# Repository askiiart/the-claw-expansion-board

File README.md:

# The Claw Expansion Board

## WARNING: EXTREME HEAT

This design accidentally used an LDO, which can lead to up to ~240 watts of excess heat being generated. Do not use this as it is now! Change the design to use a buck converter instead.

---

Would recommmend swapping it out for a XL4016E1. Will be updated with that eventually.

An expansion board to support further modding for my printer I'm desinging for Blueprint. The goals of this are:

- Power output rails on 24V, 12V, and 5V
- Power + I2C expansion port
- Laser (power/GND/PWM) port
- PNP (vacuum PWR/GND ; solenoid PWR/GND) port
- MOSFET to turn bed on/off, rather than depending on messy external setup
- Able to handle the maximum current (25A, 7.5A for buck converters) anywhere

## Parts

|Item                                |Price |Quantity|Link                                                                                 |Total Cost|Notes                                                          |
|------------------------------------|------|--------|-------------------------------------------------------------------------------------|----------|---------------------------------------------------------------|
|COS29752WU (LDO regulator)          |$2.10 |2       |https://www.lcsc.com/product-detail/C41428569.html                                   |$4.20     |                                                               |
|XD8574AP (I/O expander)             |$0.57 |1       |https://www.lcsc.com/product-detail/C561268.html                                     |$0.57     |                                                               |
|DB125-2.54-4P-GN-S (4P screw term)  |$0.40 |2       |https://www.lcsc.com/product-detail/C918122.html                                     |$0.80     |                                                               |
|DB125-2.54-3P-GN-S (3P screw term)  |$0.33 |1       |https://www.lcsc.com/product-detail/C918121.html                                     |$1.67     |                                                               |
|MS50N06 (50A NMOS)                  |$0.11 |4       |https://www.lcsc.com/product-detail/C2902884.html                                    |$0.57     |                                                               |
|AO3400A (5.8A NMOS)                 |$0.03 |1       |https://www.lcsc.com/product-detail/C347475.html                                     |$0.65     |                                                               |
|BSS84 (PMOS)                        |$0.01 |1       |https://www.lcsc.com/product-detail/C50386320.html                                   |$0.55     |                                                               |
|PZ254-3-03-Z-2.5-G0 (3x3 pins)      |$0.21 |1       |https://www.lcsc.com/product-detail/C7429377.html                                    |$1.03     |                                                               |
|XT30PW-F20.G.Y (XT30 headers)       |$0.33 |3       |https://www.lcsc.com/product-detail/C2913282.html                                    |$1.00     |                                                               |
|XT60PW-F (XT60 female headers)      |$0.55 |1       |https://www.lcsc.com/product-detail/C428722.html                                     |$0.55     |                                                               |
|XT60PW-M (XT60 male header)         |$0.52 |1       |https://www.lcsc.com/product-detail/C98732.html                                      |$0.52     |                                                               |
|S3B-XH-A(LF)(SN) (XH 3P R/A)        |$0.09 |1       |https://www.lcsc.com/product-detail/C157928.html                                     |$0.92     |                                                               |
|S4B-XH-A-1(LF)(SN) (XH 4P R/A)      |$0.15 |2       |https://www.lcsc.com/product-detail/C157925.html                                     |$0.77     |                                                               |
|SM12B-ZPDSS-TF(LF)(SN) (ZPD 12P R/A)|$0.80 |1       |https://www.lcsc.com/product-detail/C265342.html                                     |$0.80     |                                                               |
|ZPDR-12V-S (ZPD 12P housing)        |$0.34 |1       |https://www.lcsc.com/product-detail/C566944.html                                     |$1.68     |                                                               |
|HC-ZHD-T-05 (ZPD crimps)            |$0.02 |12      |https://www.lcsc.com/product-detail/C20539070.html                                   |$0.96     |                                                               |
|JST XHP-3 (XH 3P housing)           |$0.02 |2       |https://www.lcsc.com/product-detail/C144402.html                                     |$0.46     |                                                               |
|JST XHP-4 (XH 4P housing)           |$0.02 |2       |https://www.lcsc.com/product-detail/C144403.html                                     |$0.45     |                                                               |
|ZX-XH2.54-DZ (XH crimps)            |$0.01 |14      |https://www.lcsc.com/product-detail/C7462731.html                                    |$0.42     |                                                               |
|B3B-XH-A(LF)(SN) (XH 3P vertical)   |$0.05 |1       |https://www.lcsc.com/product-detail/C144394.html                                     |$0.54     |                                                               |
|ERJ1EM680E09OT (68uF caps)          |$0.03 |4       |https://www.lcsc.com/product-detail/C106558.html                                     |$0.67     |MUST be aluminum electrolytic caps, do NOT replace with ceramic|
|178MU0006 (0.1uF caps)              |$0.01 |2       |https://www.lcsc.com/product-detail/C5632430.html                                    |$0.69     |                                                               |
|MF1/4W-10K±1%-ST52 (10k resistor)   |$0.01 |7       |https://www.lcsc.com/product-detail/C2903232.html                                    |$0.59     |All resistors are highly accurate due to setting LDO regulators|
|MF1/4W-8K2±1%-ST52 (8.2k resistor)  |$0.00 |1       |https://www.lcsc.com/product-detail/C2848599.html                                    |$0.49     |                                                               |
|MF1/8W-3K3±1%-ST52 (3.3k resistor)  |$0.01 |1       |https://www.lcsc.com/product-detail/C2903352.html                                    |$0.50     |                                                               |
|MF1/4W-1K±1%-ST52 (1k resistor)     |$0.01 |1       |https://www.lcsc.com/product-detail/C2903245.html                                    |$0.56     |                                                               |
|MF1/4W-470Ω±1% T (470 resistor)     |$0.01 |1       |https://www.lcsc.com/product-detail/C119317.html                                     |$0.58     |                                                               |
|1N4148TR (diode)                    |$0.02 |1       |https://www.lcsc.com/product-detail/C84410.html                                      |$0.80     |                                                               |
|2.54mm jumpers                      |$0.01 |4       |https://www.lcsc.com/product-detail/C2998928.html                                    |$0.44     |                                                               |
|TMP100NA/3K (temp sensor)           |$0.46 |1       |https://www.lcsc.com/product-detail/C31810.html                                      |$0.46     |                                                               |
|9733 24V fan                        |$6.39 |1       |https://www.aliexpress.us/item/3256804645826698.html                                 |$6.39     |                                                               |
|Wire crimping tool                  |$15.99|1       |https://www.amazon.com/Crimping-Amliber-Connectors-Electrical-Terminals/dp/B0D1FR76Q7|$15.99    |                                                               |
|                                    |      |        |                                                                                     |          |                                                               |
|Subtotal                            |      |        |                                                                                     |$47.28    |                                                               |
|                                    |      |        |                                                                                     |          |                                                               |
|JLCPCB                              |      |        |                                                                                     |$7.30     |                                                               |
|LCSC shipping                       |      |        |                                                                                     |$14.56    |                                                               |
|                                    |      |        |                                                                                     |          |                                                               |
|Total                               |      |        |                                                                                     |$74.84    |                                                               |

## Notes

- **The case will be made by hand out of wood**, not 3D printed, due to potential for high temperatures. As such there is obviously no CAD model.
- **XT60 polarity is reversed!!!** I don't have the time (or energy) to redo the entire board right now, but I may redo it later.
  - XT30 has been fixed, that does not apply here
  - BOM may change slightly, as when I fix that I will make the 24V input male. Cost should be slightly lower.
- Some 3D models don't exist, and so those components aren't in the render.

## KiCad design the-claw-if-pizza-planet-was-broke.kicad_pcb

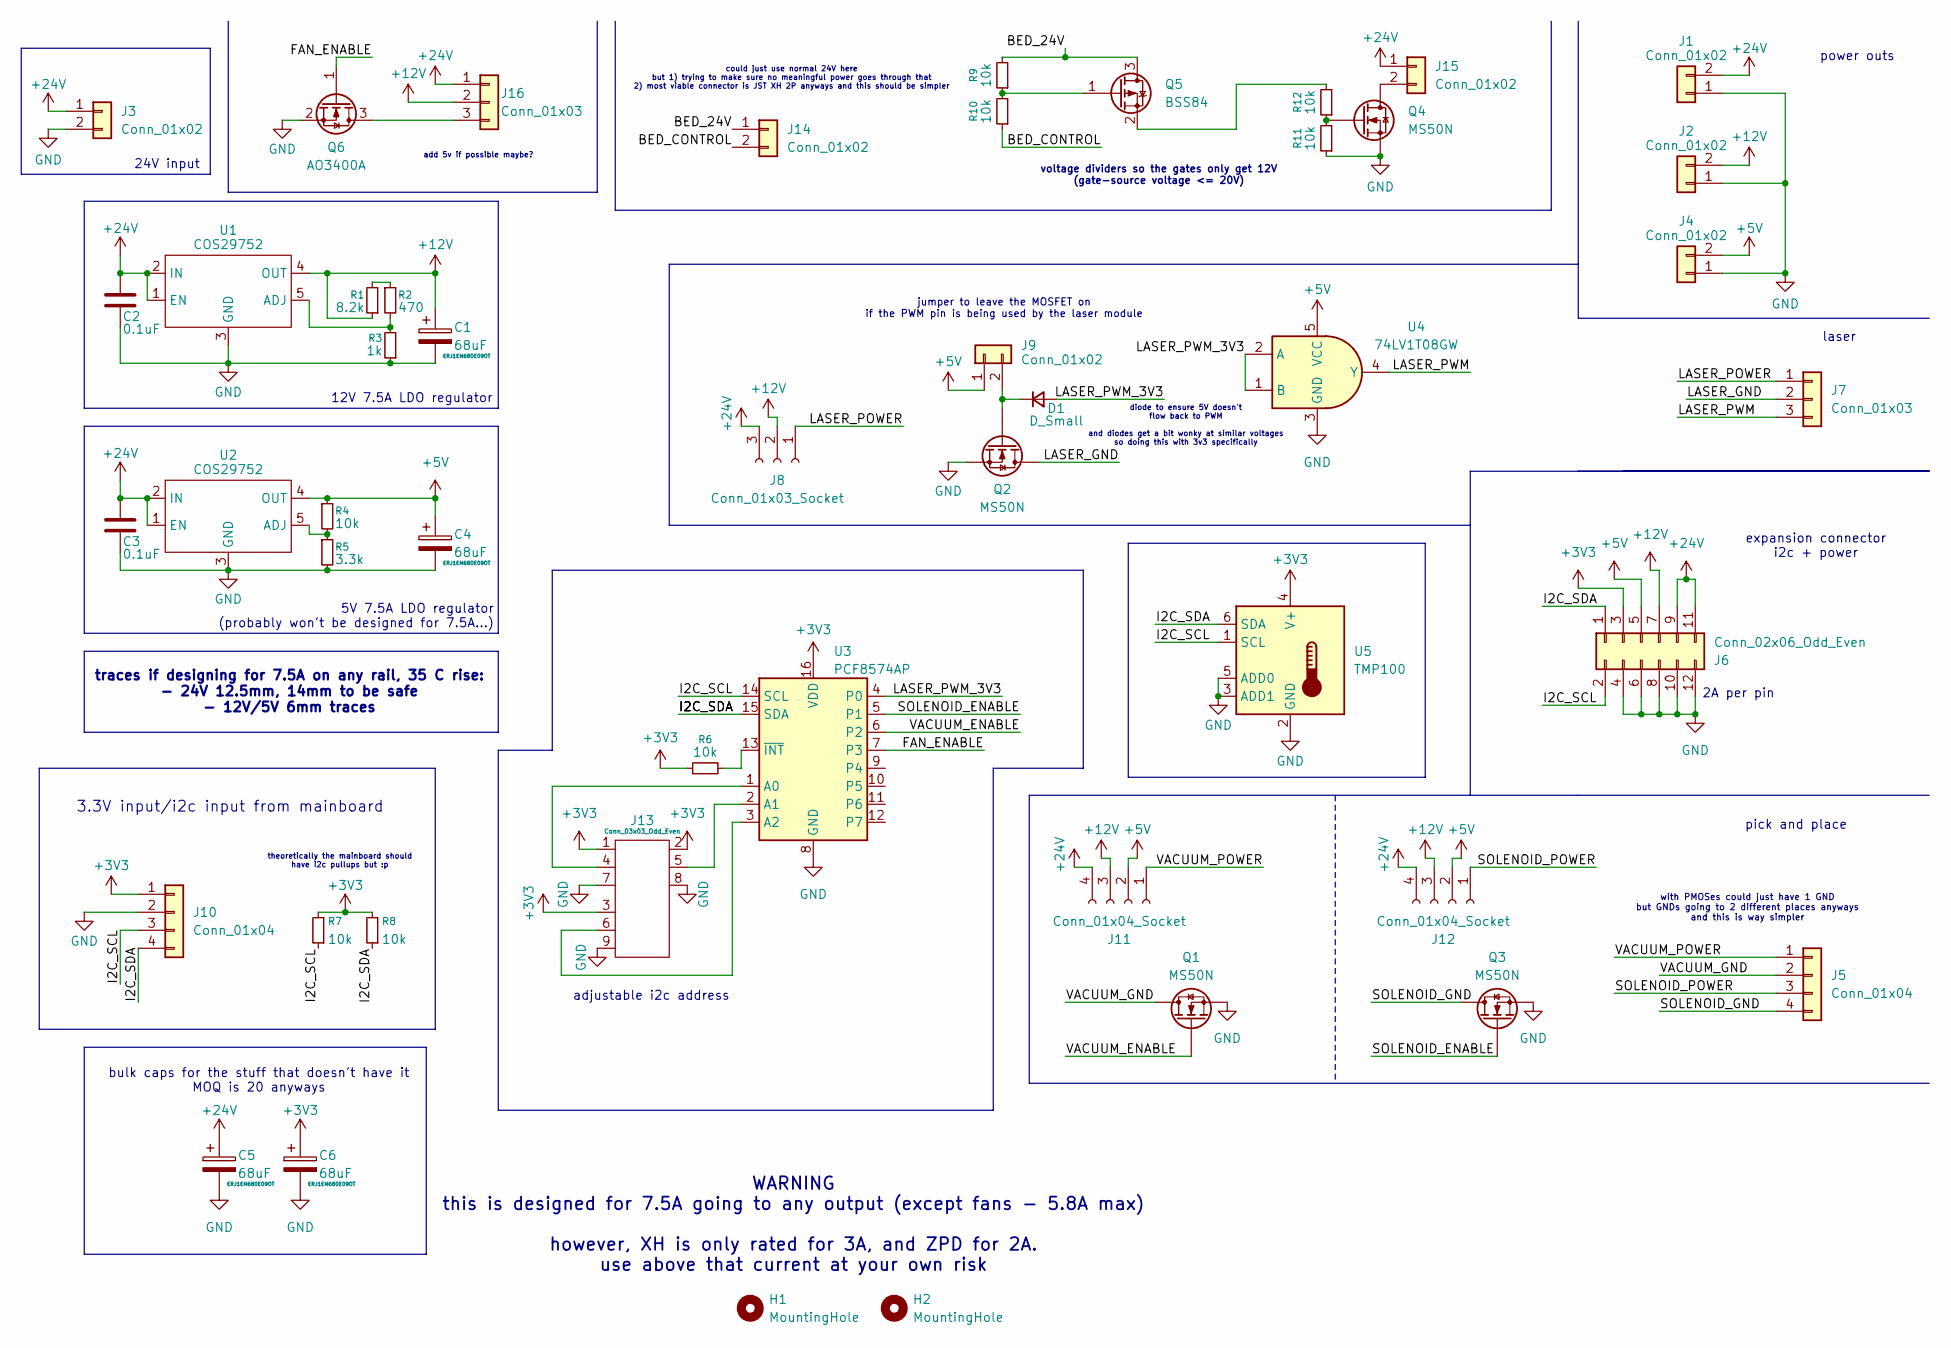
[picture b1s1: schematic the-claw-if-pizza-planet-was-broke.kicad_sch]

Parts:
C1, C4, C5, C6: 68uF; CP_Radial_D6.3mm_P2.50mm
C2, C3: 0.1uF; R_Axial_DIN0204_L3.6mm_D1.6mm_P2.54mm_Vertical
D1: D_Small; D_DO-35_SOD27_P7.62mm_Horizontal
H1, H2: MountingHole; MountingHole_4.3mm_M4
J1, J2, J4: Conn_01x02; AMASS_XT30PW-F_1x02_P2.50mm_Horizontal
J3: Conn_01x02; AMASS_XT60PW-M_1x02_P7.20mm_Horizontal
J5, J10: Conn_01x04; JST_XH_S4B-XH-A-1_1x04_P2.50mm_Horizontal
J6: Conn_02x06_Odd_Even; CONN-SM12B-ZPDSS-TF
J7: Conn_01x03; JST_XH_S3B-XH-A_1x03_P2.50mm_Horizontal
J8: Conn_01x03_Socket; DB125-2.54-3P
J9: Conn_01x02; PinHeader_1x02_P2.54mm_Vertical
J11, J12: Conn_01x04_Socket; DB125-2.54-4P
J13: Conn_03x03_Odd_Even; PinHeader_3x03_P2.54mm_Vertical
J14: Conn_01x02; JST_XH_S2B-XH-A-1_1x02_P2.50mm_Horizontal
J15: Conn_01x02; AMASS_XT60PW-F_1x02_P7.20mm_Horizontal
J16: Conn_01x03; JST_XH_B3B-XH-A_1x03_P2.50mm_Vertical
Q1, Q2, Q3, Q4: MS50N; TO-252-2
Q5: BSS84; SOT-23
Q6: AO3400A; SOT-23
R1: 8.2k; R_Axial_DIN0207_L6.3mm_D2.5mm_P10.16mm_Horizontal
R2: 470; R_Axial_DIN0207_L6.3mm_D2.5mm_P10.16mm_Horizontal
R3: 1k; R_Axial_DIN0207_L6.3mm_D2.5mm_P10.16mm_Horizontal
R4, R6, R7, R8, R9, R10, R11, R12: 10k; R_Axial_DIN0207_L6.3mm_D2.5mm_P10.16mm_Horizontal
R5: 3.3k; R_Axial_DIN0204_L3.6mm_D1.6mm_P5.08mm_Horizontal
U1, U2: COS29752; TO-263-5_TabPin3
U3: PCF8574AP; DIP-16_W7.62mm
U4: 74LV1T08GW; SOT-353_SC-70-5
U5: TMP100; SOT-23-6

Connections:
+3V3: C6.1, J6.3, J10.1, J13.1, J13.2, J13.3, R6.1, R7.2, R8.2, U3.16 (VDD), U5.4 (V+)
+5V: C4.1, J4.2, J6.5, J9.1, J11.2, J12.2, R4.1, U2.4 (OUT), U4.5 (VCC)
+12V: C1.1, J2.2, J6.7, J8.2, J11.3, J12.3, J16.2, R1.1, U1.4 (OUT)
+24V: C2.2, C3.2, C5.1, J1.2, J3.1, J6.9, J6.11, J8.3, J11.4, J12.4, J15.1, J16.1, U1.1 (EN), U1.2 (IN), U2.1 (EN), U2.2 (IN)
/BED_24V: J14.1, Q5.3 (D), R9.2
/BED_CONTROL: J14.2, R10.1
/FAN_ENABLE: Q6.1 (G), U3.7 (P3)
/I2C_SCL: J6.2, J10.3, R7.1, U3.14 (SCL), U5.1 (SCL)
/I2C_SDA: J6.1, J10.4, R8.1, U3.15 (SDA), U5.6 (SDA)
/LASER_GND: J7.2, Q2.2 (D)
/LASER_POWER: J7.1, J8.1
/LASER_PWM: J7.3, U4.4 (Y)
/LASER_PWM_3V3: D1.2 (A), U3.4 (P0), U4.1 (B), U4.2 (A)
/SOLENOID_ENABLE: Q3.1 (G), U3.5 (P1)
/SOLENOID_GND: J5.4, Q3.2 (D)
/SOLENOID_POWER: J5.3, J12.1
/VACUUM_ENABLE: Q1.1 (G), U3.6 (P2)
/VACUUM_GND: J5.2, Q1.2 (D)
/VACUUM_POWER: J5.1, J11.1
GND: C1.2, C2.1, C3.1, C4.2, C5.2, C6.2, J1.1, J2.1, J3.2, J4.1, J6.4, J6.6, J6.8, J6.10, J6.12, J10.2, J13.7, J13.8, J13.9, Q1.3 (S), Q2.3 (S), Q3.3 (S), Q4.3 (S), Q6.2 (S), R3.1, R5.2, R11.1, U1.3 (GND), U2.3 (GND), U3.8 (GND), U4.3 (GND), U5.2 (GND), U5.3 (ADD1), U5.5 (ADD0)
unnamed: D1.1 (K), J9.2, Q2.1 (G)
unnamed: J15.2, Q4.2 (D)
unnamed: J16.3, Q6.3 (D)
unnamed: Q4.1 (G), R11.2, R12.1
unnamed: Q5.1 (G), R9.1, R10.2
unnamed: Q5.2 (S), R12.2
unnamed: R1.2, R2.1
unnamed: R2.2, R3.2, U1.5 (ADJ)
unnamed: R4.2, R5.1, U2.5 (ADJ)
unnamed: J13.4, U3.1 (A0)
unnamed: J13.5, U3.2 (A1)
unnamed: J13.6, U3.3 (A2)
unnamed: R6.2, U3.13 (~INT)

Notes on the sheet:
power outs
traces if designing for 7.5A on any rail, 35 C rise: - 24V 12.5mm, 14mm to be safe - 12V/5V 6mm traces
WARNING this is designed for 7.5A going to any output (except fans - 5.8A max) however, XH is only rated for 3A, and ZPD for 2A. use above that current at your own risk
pick and place
laser
diode to ensure 5V doesn't flow back to PWM and diodes get a bit wonky at similar voltages so doing this with 3v3 specifically
voltage dividers so the gates only get 12V (gate-source voltage <= 20V)
could just use normal 24V here but 1) trying to make sure no meaningful power goes through that 2) most viable connector is JST XH 2P anyways and this should be simpler
5V 7.5A LDO regulator (probably won't be designed for 7.5A...)
3.3V input/i2c input from mainboard
12V 7.5A LDO regulator
with PMOSes could just have 1 GND but GNDs going to 2 different places anyways and this is way simpler
theoretically the mainboard should have i2c pullups but :p
jumper to leave the MOSFET on if the PWM pin is being used by the laser module
24V input
expansion connector i2c + power
adjustable i2c address
bulk caps for the stuff that doesn't have it MOQ is 20 anyways
add 5v if possible maybe?
2A per pin

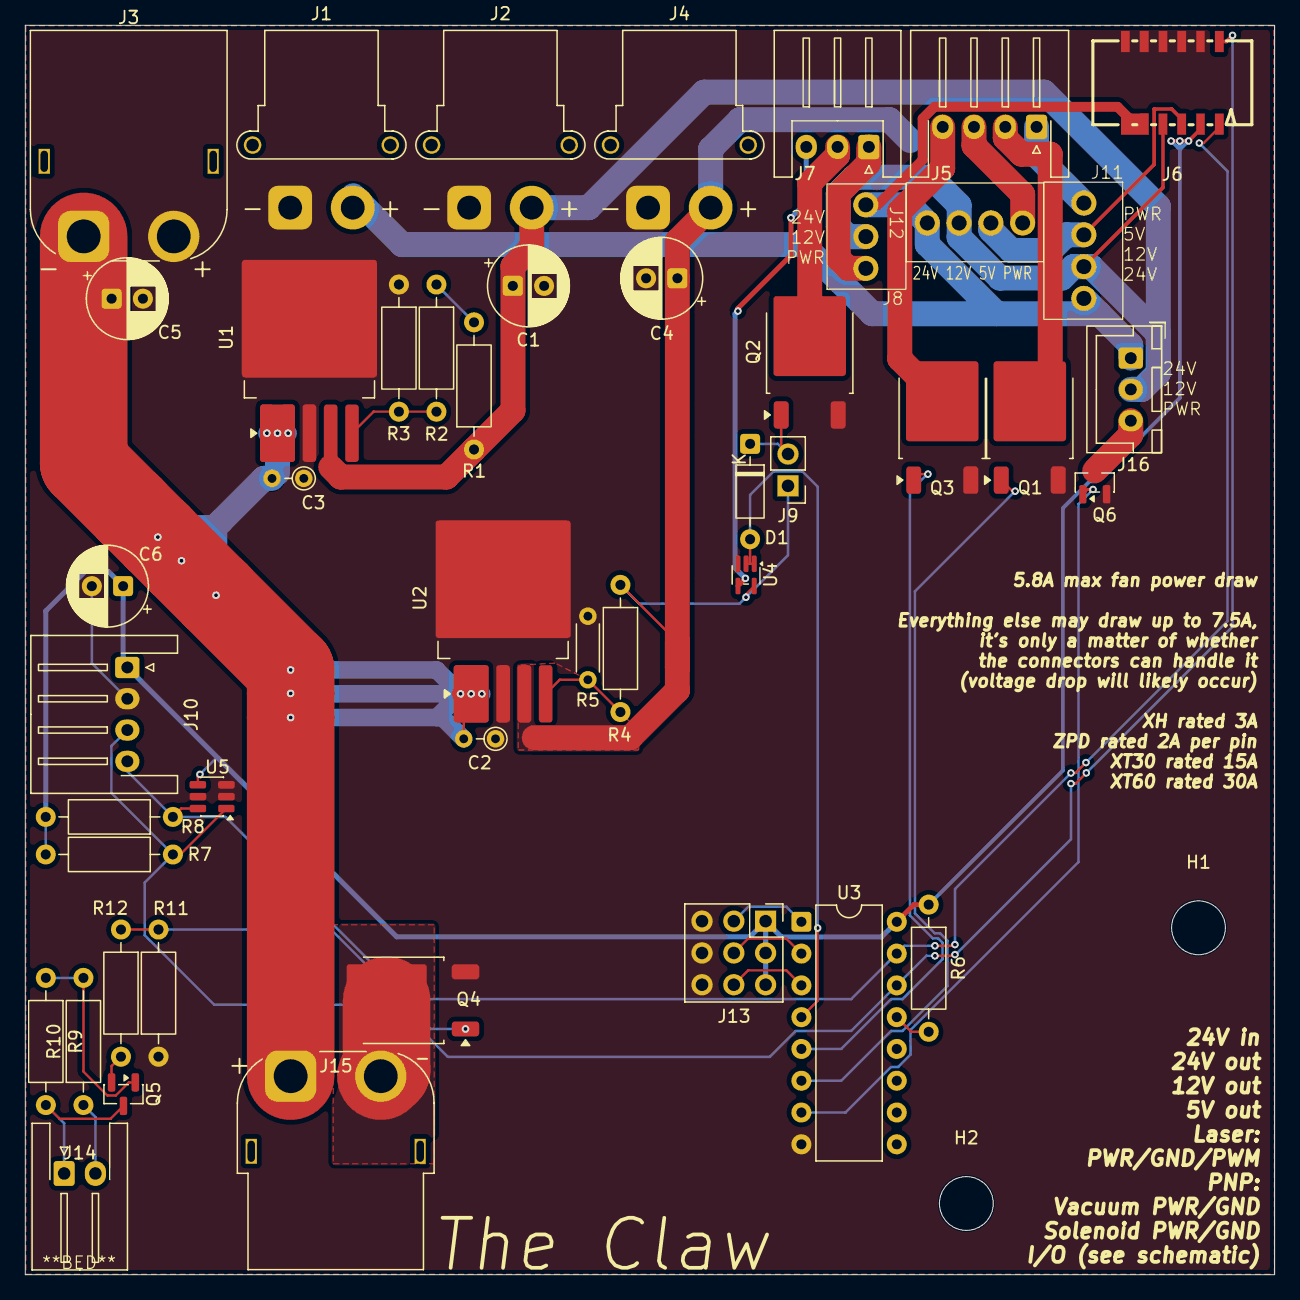
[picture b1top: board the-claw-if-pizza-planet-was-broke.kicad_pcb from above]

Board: 2 copper layers, 99.8 x 99.8 mm, 48 parts (0 on the bottom side), 33 nets.

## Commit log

2026-03-19 initial commit - schematic done
2026-03-20 update with finished(?) pcb
2026-03-21 fix a bunch of stuff
2026-03-21 add 3d models
2026-03-21 give XT30 hrt
2026-03-21 add BOM and stuff
2026-03-21 fix BOM links
2026-05-07 update w/ XT60 + silkscreen improvement
2026-05-14 OH GOD I USED LDOs
2026-05-14 add recommended buck converter
2026-05-22 update warning message to be more helpful lol
